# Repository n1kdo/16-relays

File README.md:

# 16-relays

This is a board that allows a Raspberry Pi Pico-W to control 16 SPST relays.

The original purpose is to provide better automation for a 2-in, 6-out remote antenna switch, but
it is built with extra capacity to allow a 2-in, 8-out remote switch as well.

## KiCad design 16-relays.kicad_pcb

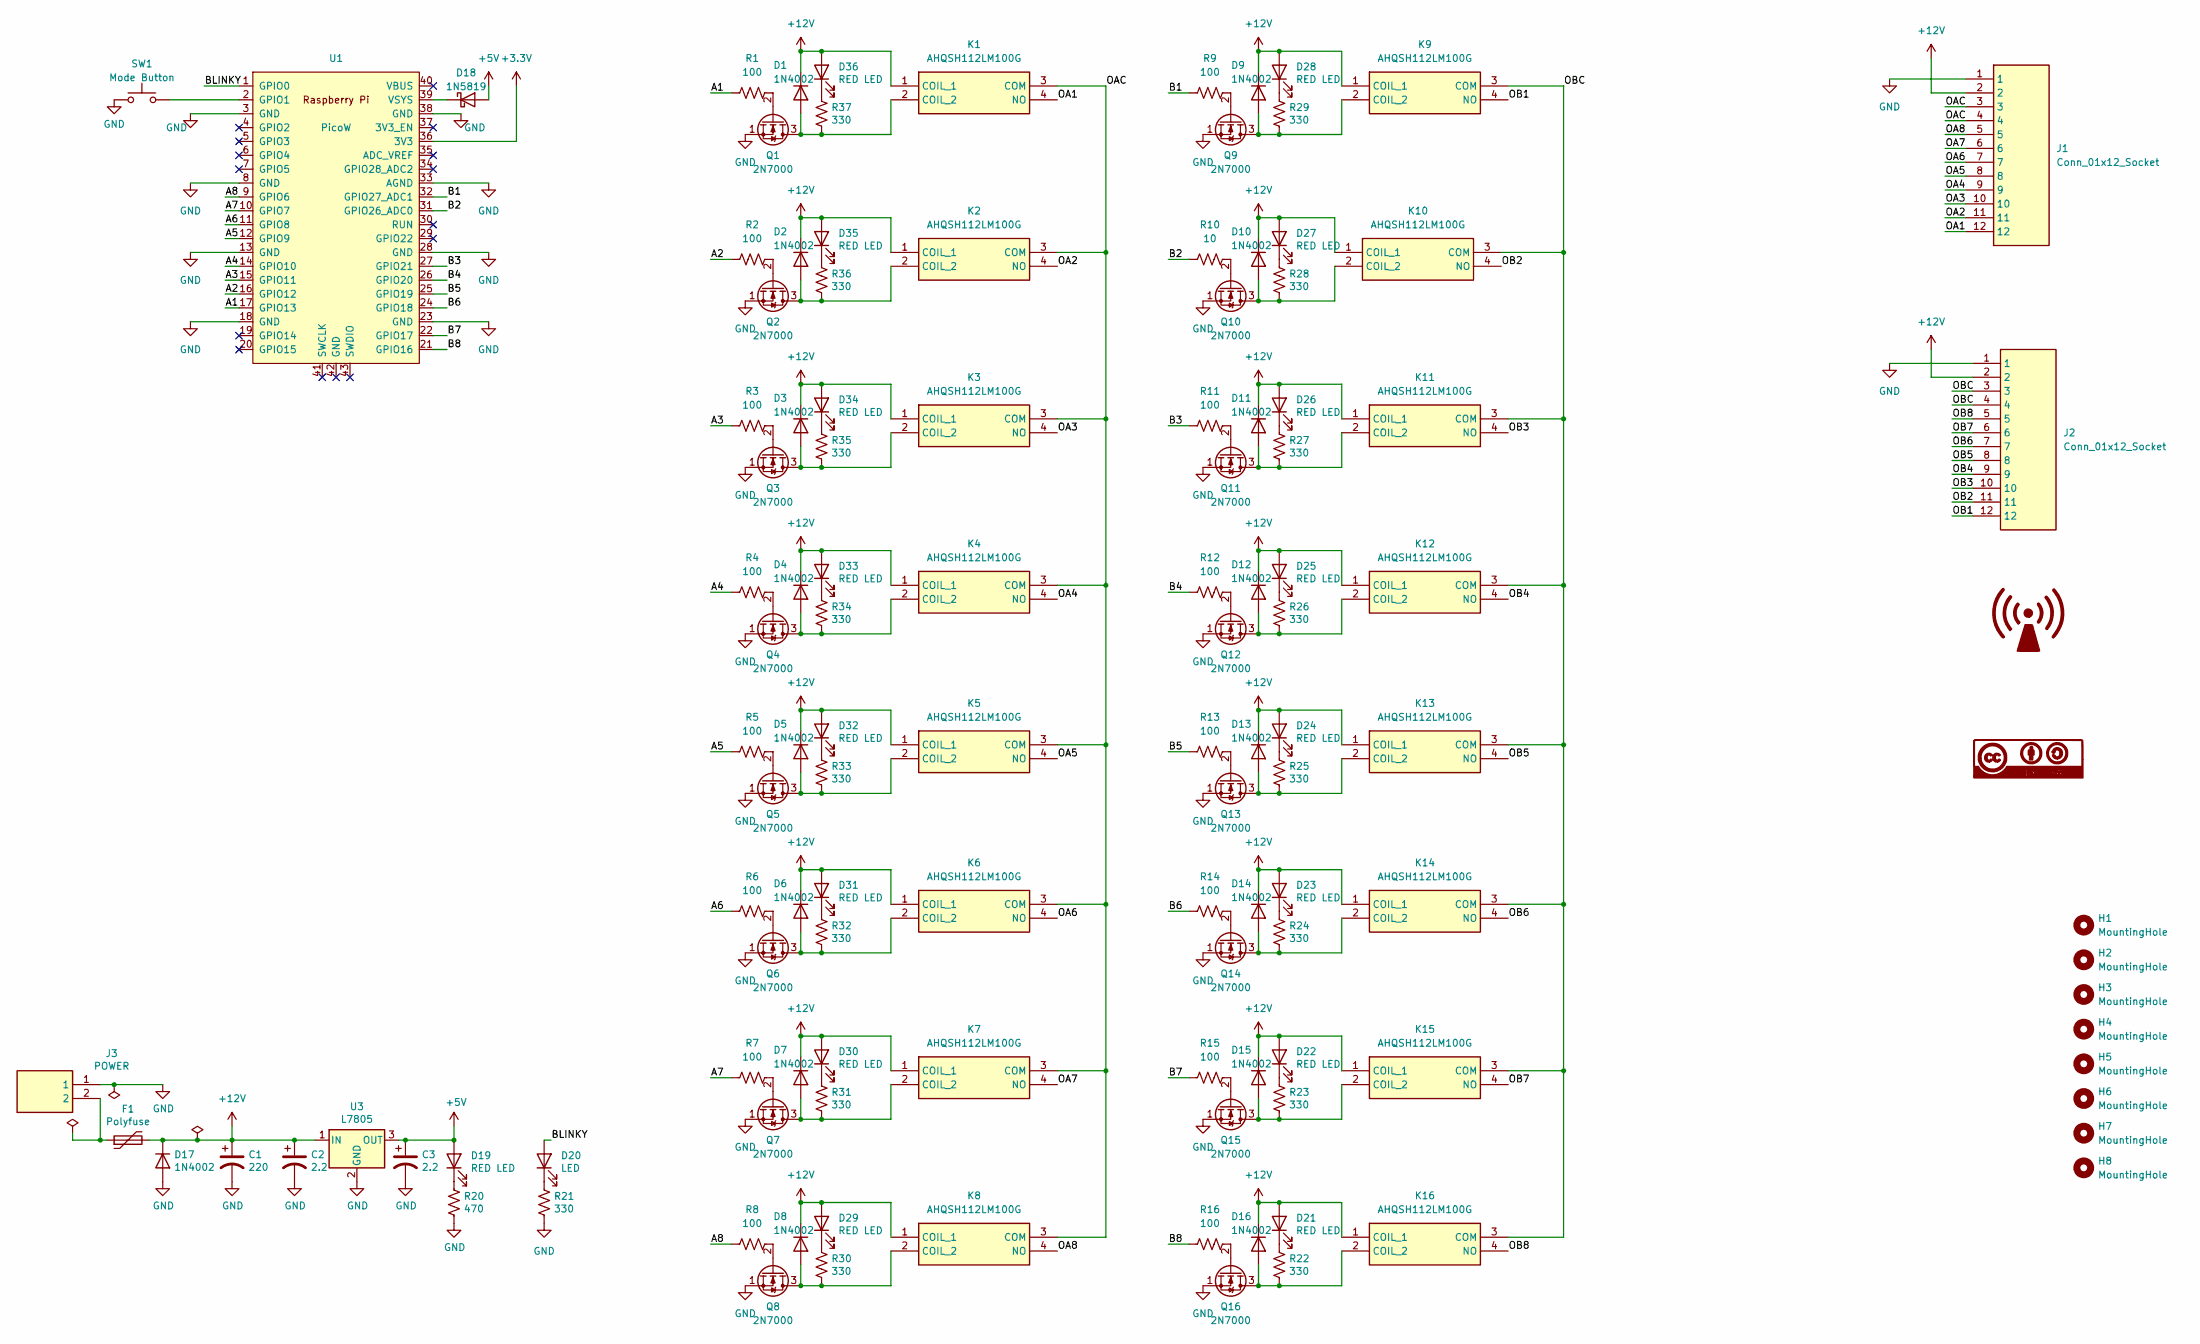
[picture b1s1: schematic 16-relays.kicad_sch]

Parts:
C1: 220; CP_Radial_D8.0mm_P3.50mm; Part ECA-1EM221
C2, C3: 2.2; CP_Radial_D5.0mm_P2.50mm; Part EEU-FC1H2R2H
D1, D2, D3, D4, D5, D6, D7, D8, D9, D10, D11, D12, D13, D14, D15, D16: 1N4002; D_DO-41_SOD81_P7.62mm_Horizontal
D17: 1N4002; D_DO-15_P10.16mm_Horizontal; Part 1n4002
D18: 1N5819; D_DO-41_SOD81_P10.16mm_Horizontal
D19: RED LED; LED_D3.0mm
D20: LED; LED_D3.0mm
D21, D22, D23, D24, D25, D26, D27, D28, D29, D30, D31, D32, D33, D34, D35, D36: RED LED; LED_D3.0mm; Part AP2012HD
F1: Polyfuse; RUEF090; Part 30R090UU
H1, H2, H3, H4, H5, H6, H7, H8: MountingHole; MountingHole_3.5mm_Pad
J1, J2: Conn_01x12_Socket; 705530116; Mouser Part Number 538-70553-0116
J3: POWER; 705530001; Part 26-60-4020; Mouser Part Number 538-70553-0001
K1, K2, K3, K4, K5, K6, K7, K8, K9, K10, K11, K12, K13, K14, K15, K16: AHQSH112LM100G; AHQSH112LM112G; Mouser Part Number 523-AHQSH105LM100G
Q1, Q2, Q3, Q4, Q5, Q6, Q7, Q8, Q9, Q10, Q11, Q12, Q13, Q14, Q15, Q16: 2N7000; TO-92_Inline
R1, R2, R3, R4, R5, R6, R7, R8, R9, R11, R12, R13, R14, R15, R16: 100; R_Axial_DIN0207_L6.3mm_D2.5mm_P7.62mm_Horizontal
R10: 10; R_Axial_DIN0207_L6.3mm_D2.5mm_P7.62mm_Horizontal
R20: 470; R_Axial_DIN0207_L6.3mm_D2.5mm_P7.62mm_Horizontal; Part ERJ-6GEYJ471V
R21, R22, R23, R24, R25, R26, R27, R28, R29, R30, R31, R32, R33, R34, R35, R36, R37: 330; R_Axial_DIN0207_L6.3mm_D2.5mm_P7.62mm_Horizontal; Part ERJ-6GEYJ471V
SW1: Mode Button; GB215AHB; part GB215AH
U1: PicoW; RPi_PicoW_SMD_TH
U3: L7805; TO-220-3_Vertical; Part L7805CDT-TR

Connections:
+3.3V: U1.36 (3V3)
+5V: C3.1, D18.2 (A), D19.2 (A), U3.3 (OUT)
+12V: C1.1, C2.1, D1.1 (K), D2.1 (K), D3.1 (K), D4.1 (K), D5.1 (K), D6.1 (K), D7.1 (K), D8.1 (K), D9.1 (K), D10.1 (K), D11.1 (K), D12.1 (K), D13.1 (K), D14.1 (K), D15.1 (K), D16.1 (K), D17.1 (K), D21.2 (A), D22.2 (A), D23.2 (A), D24.2 (A), D25.2 (A), D26.2 (A), D27.2 (A), D28.2 (A), D29.2 (A), D30.2 (A), D31.2 (A), D32.2 (A), D33.2 (A), D34.2 (A), D35.2 (A), D36.2 (A), F1.2, J1.2, J2.2, K1.1 (COIL_1), K2.1 (COIL_1), K3.1 (COIL_1), K4.1 (COIL_1), K5.1 (COIL_1), K6.1 (COIL_1), K7.1 (COIL_1), K8.1 (COIL_1), K9.1 (COIL_1), K10.1 (COIL_1), K11.1 (COIL_1), K12.1 (COIL_1), K13.1 (COIL_1), K14.1 (COIL_1), K15.1 (COIL_1), K16.1 (COIL_1), U3.1 (IN)
/A1: R1.1, U1.17 (GPIO13)
/A2: R2.1, U1.16 (GPIO12)
/A3: R3.1, U1.15 (GPIO11)
/A4: R4.1, U1.14 (GPIO10)
/A5: R5.1, U1.12 (GPIO9)
/A6: R6.1, U1.11 (GPIO8)
/A7: R7.1, U1.10 (GPIO7)
/A8: R8.1, U1.9 (GPIO6)
/B1: R9.1, U1.32 (GPIO27_ADC1)
/B2: R10.1, U1.31 (GPIO26_ADC0)
/B3: R11.1, U1.27 (GPIO21)
/B4: R12.1, U1.26 (GPIO20)
/B5: R13.1, U1.25 (GPIO19)
/B6: R14.1, U1.24 (GPIO18)
/B7: R15.1, U1.22 (GPIO17)
/B8: R16.1, U1.21 (GPIO16)
/BLINKY: D20.2 (A), U1.1 (GPIO0)
/OA1: J1.12, K1.4 (NO)
/OA2: J1.11, K2.4 (NO)
/OA3: J1.10, K3.4 (NO)
/OA4: J1.9, K4.4 (NO)
/OA5: J1.8, K5.4 (NO)
/OA6: J1.7, K6.4 (NO)
/OA7: J1.6, K7.4 (NO)
/OA8: J1.5, K8.4 (NO)
/OAC: J1.3, J1.4, K1.3 (COM), K2.3 (COM), K3.3 (COM), K4.3 (COM), K5.3 (COM), K6.3 (COM), K7.3 (COM), K8.3 (COM)
/OB1: J2.12, K9.4 (NO)
/OB2: J2.11, K10.4 (NO)
/OB3: J2.10, K11.4 (NO)
/OB4: J2.9, K12.4 (NO)
/OB5: J2.8, K13.4 (NO)
/OB6: J2.7, K14.4 (NO)
/OB7: J2.6, K15.4 (NO)
/OB8: J2.5, K16.4 (NO)
/OBC: J2.3, J2.4, K9.3 (COM), K10.3 (COM), K11.3 (COM), K12.3 (COM), K13.3 (COM), K14.3 (COM), K15.3 (COM), K16.3 (COM)
GND: C1.2, C2.2, C3.2, D17.2 (A), J1.1, J2.1, J3.1, Q1.1 (S), Q2.1 (S), Q3.1 (S), Q4.1 (S), Q5.1 (S), Q6.1 (S), Q7.1 (S), Q8.1 (S), Q9.1 (S), Q10.1 (S), Q11.1 (S), Q12.1 (S), Q13.1 (S), Q14.1 (S), Q15.1 (S), Q16.1 (S), R20.2, R21.2, SW1.1, U1.3 (GND), U1.8 (GND), U1.13 (GND), U1.18 (GND), U1.23 (GND), U1.28 (GND), U1.33 (AGND), U1.38 (GND), U3.2 (GND)
unnamed: D1.2 (A), K1.2 (COIL_2), Q1.3 (D), R37.2
unnamed: D2.2 (A), K2.2 (COIL_2), Q2.3 (D), R36.2
unnamed: D3.2 (A), K3.2 (COIL_2), Q3.3 (D), R35.2
unnamed: D4.2 (A), K4.2 (COIL_2), Q4.3 (D), R34.2
unnamed: D5.2 (A), K5.2 (COIL_2), Q5.3 (D), R33.2
unnamed: D6.2 (A), K6.2 (COIL_2), Q6.3 (D), R32.2
unnamed: D7.2 (A), K7.2 (COIL_2), Q7.3 (D), R31.2
unnamed: D8.2 (A), K8.2 (COIL_2), Q8.3 (D), R30.2
unnamed: D9.2 (A), K9.2 (COIL_2), Q9.3 (D), R29.2
unnamed: D10.2 (A), K10.2 (COIL_2), Q10.3 (D), R28.2
unnamed: D11.2 (A), K11.2 (COIL_2), Q11.3 (D), R27.2
unnamed: D12.2 (A), K12.2 (COIL_2), Q12.3 (D), R26.2
unnamed: D13.2 (A), K13.2 (COIL_2), Q13.3 (D), R25.2
unnamed: D14.2 (A), K14.2 (COIL_2), Q14.3 (D), R24.2
unnamed: D15.2 (A), K15.2 (COIL_2), Q15.3 (D), R23.2
unnamed: D16.2 (A), K16.2 (COIL_2), Q16.3 (D), R22.2
unnamed: D18.1 (K), U1.39 (VSYS)
unnamed: D19.1 (K), R20.1
unnamed: D20.1 (K), R21.1
unnamed: D21.1 (K), R22.1
unnamed: D22.1 (K), R23.1
unnamed: D23.1 (K), R24.1
unnamed: D24.1 (K), R25.1
unnamed: D25.1 (K), R26.1
unnamed: D26.1 (K), R27.1
unnamed: D27.1 (K), R28.1
unnamed: D28.1 (K), R29.1
unnamed: D29.1 (K), R30.1
unnamed: D30.1 (K), R31.1
unnamed: D31.1 (K), R32.1
unnamed: D32.1 (K), R33.1
unnamed: D33.1 (K), R34.1
unnamed: D34.1 (K), R35.1
unnamed: D35.1 (K), R36.1
unnamed: D36.1 (K), R37.1
unnamed: F1.1, J3.2
unnamed: Q1.2 (G), R1.2
unnamed: Q2.2 (G), R2.2
unnamed: Q3.2 (G), R3.2
unnamed: Q4.2 (G), R4.2
unnamed: Q5.2 (G), R5.2
unnamed: Q6.2 (G), R6.2
unnamed: Q7.2 (G), R7.2
unnamed: Q8.2 (G), R8.2
unnamed: Q9.2 (G), R9.2
unnamed: Q10.2 (G), R10.2
unnamed: Q11.2 (G), R11.2
unnamed: Q12.2 (G), R12.2
unnamed: Q13.2 (G), R13.2
unnamed: Q14.2 (G), R14.2
unnamed: Q15.2 (G), R15.2
unnamed: Q16.2 (G), R16.2
unnamed: SW1.2, U1.2 (GPIO1)

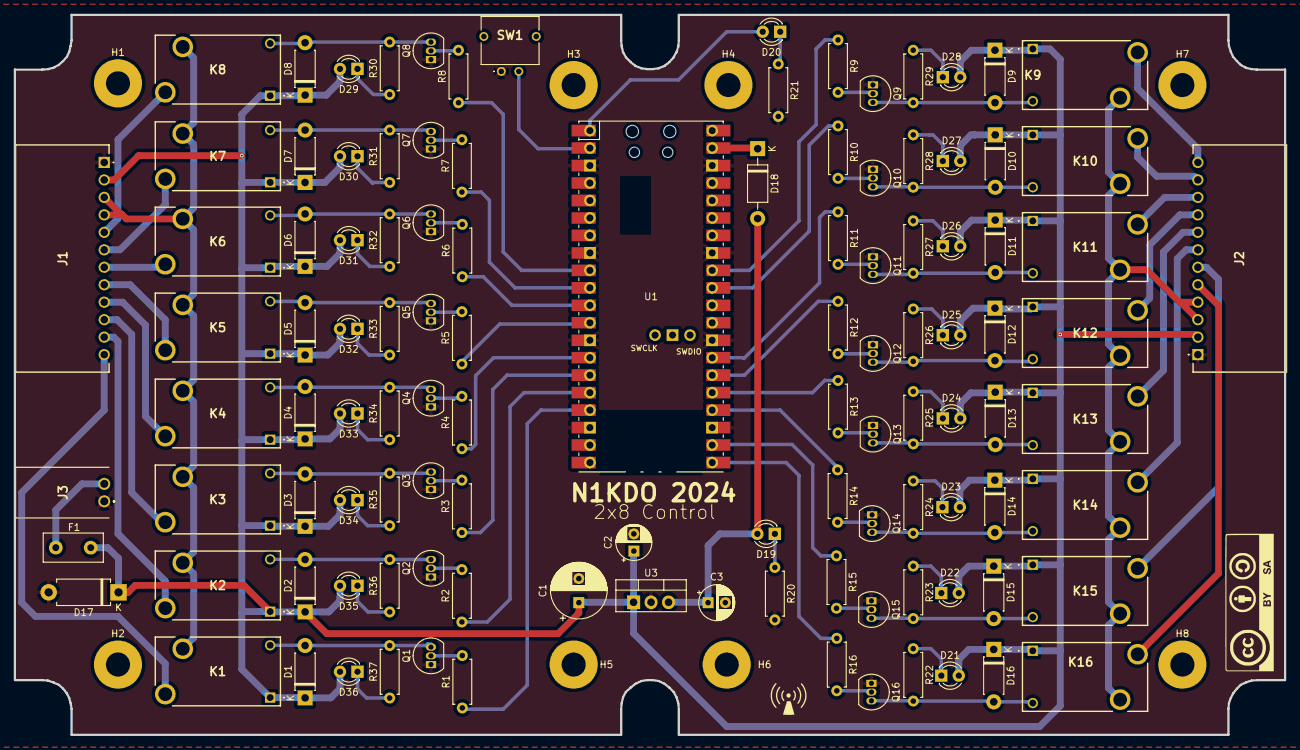
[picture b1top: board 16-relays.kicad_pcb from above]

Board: 2 copper layers, 184.7 x 104.7 mm, 121 parts (0 on the bottom side), 91 nets.

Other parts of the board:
Ref**: Val**; CC-BY-SA

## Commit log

2024-07-14 schematic and pcb commit
2024-07-14 add 3d image
2024-07-20 Update 16-relays.kicad_sch
    adjust LED current limiting resistors
2024-08-04 add doc

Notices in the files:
16-relays.kicad_pcb:
N1KDO 2024 CC-By-SA
